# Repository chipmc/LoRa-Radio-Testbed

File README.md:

# LoRa-Radio-Testbed
# This repository includes the Arduino C programs for a simple LoRa testbed I created
# The Moteino LoRa Page has great information on this radio: https://lowpowerlab.com/moteino/#lora
#     - To use these sketches, you can download the libraries here:
#     - https://lowpowerlab.com/RadioHead_LowPowerLab.zip
# The hardware is described in the attached EAGLE files

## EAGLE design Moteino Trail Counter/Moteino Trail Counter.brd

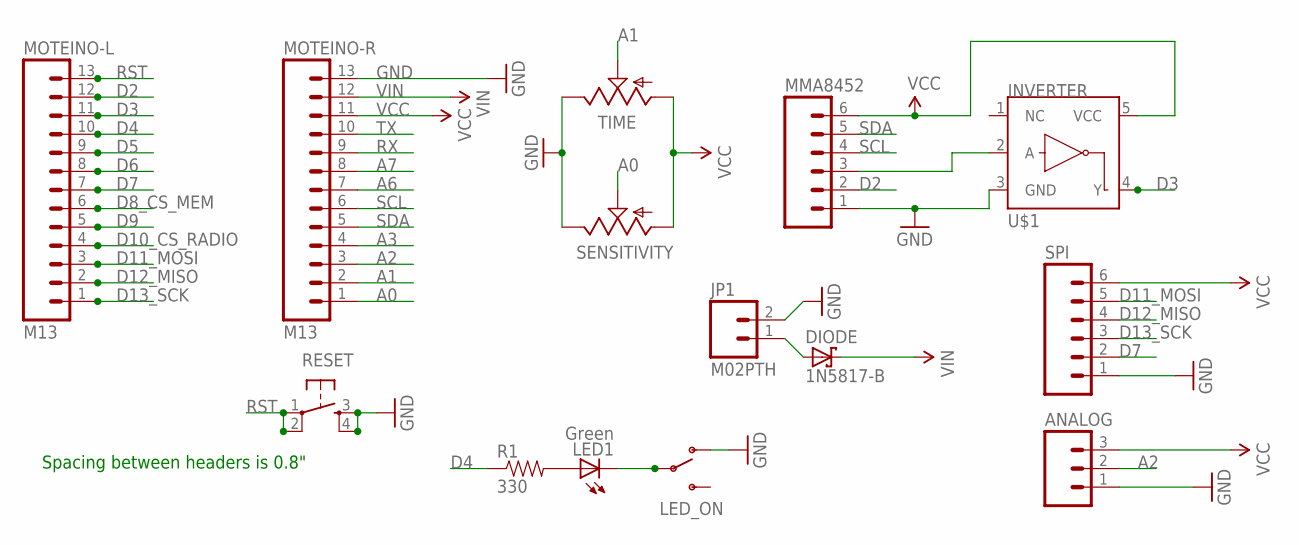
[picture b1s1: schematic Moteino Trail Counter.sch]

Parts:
ANALOG: M03LOCK; 1X03_LOCK
DIODE: 1N5817-B; DO41-7.6
JP1: M02PTH; 1X02
LED1: Green; LED3MM
LED_ON: SWITCH-SPDTPTH; SWITCH-SPDT
MMA8452: M06LOCK; 1X06_LOCK
MOTEINO-L: M13; 1X13
MOTEINO-R: M13; 1X13
R1: 330; AXIAL-0.3
RESET: TAC_SWITCHPTH; TACTILE-PTH
SENSITIVITY: TRIM_US-B25U; B25U
SPI: M06LOCK; 1X06_LOCK
TIME: TRIM_US-B25U; B25U
U$1: INVERTER; SOT23-5

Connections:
A0: MOTEINO-R.1, SENSITIVITY.S
A1: MOTEINO-R.2, TIME.S
A2: ANALOG.2, MOTEINO-R.3
A3: MOTEINO-R.4
A6: MOTEINO-R.7
A7: MOTEINO-R.8
D2: MMA8452.2, MOTEINO-L.12
D3: MOTEINO-L.11, U$1.4 (Y)
D4: MOTEINO-L.10, R1.P$1 (1)
D5: MOTEINO-L.9
D6: MOTEINO-L.8
D7: MOTEINO-L.7, SPI.2
D8_CS_MEM: MOTEINO-L.6
D9: MOTEINO-L.5
D10_CS_RADIO: MOTEINO-L.4
D11_MOSI: MOTEINO-L.3, SPI.5
D12_MISO: MOTEINO-L.2, SPI.4
D13_SCK: MOTEINO-L.1, SPI.3
GND: ANALOG.1, JP1.2, LED_ON.1 (O), MMA8452.1, MOTEINO-R.13, RESET.3, RESET.4, SENSITIVITY.E, SPI.1, TIME.E, U$1.3 (GND)
unnamed: DIODE.A, JP1.1
unnamed: LED1.A, R1.P$2 (2)
unnamed: MMA8452.3, U$1.2 (A)
unnamed: LED1.K (C), LED_ON.2
RST: MOTEINO-L.13, RESET.1, RESET.2
RX: MOTEINO-R.9
SCL: MMA8452.4, MOTEINO-R.6
SDA: MMA8452.5, MOTEINO-R.5
TX: MOTEINO-R.10
VCC: ANALOG.3, MMA8452.6, MOTEINO-R.11, SENSITIVITY.A, SPI.6, TIME.A, U$1.5 (VCC)
VIN: DIODE.C, MOTEINO-R.12

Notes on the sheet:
Spacing between headers is 0.8"

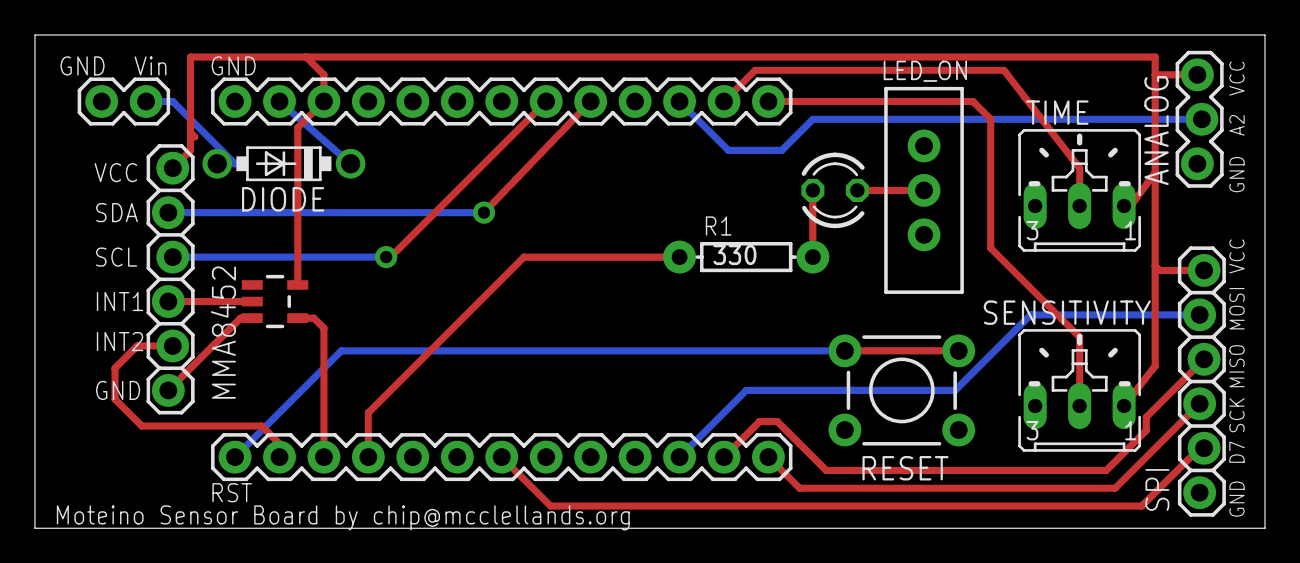
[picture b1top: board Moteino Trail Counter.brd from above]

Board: 2 copper layers, 70.3 x 28.2 mm, 14 parts (0 on the bottom side), 20 nets.

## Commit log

2016-09-13 Loaded Arduino and EAGLE files for Project
2016-09-13 Create README.md
    Added descriptions
2016-09-13 gitignore added

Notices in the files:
parts and their libraries:
SparkFun-Connectors: Licensing: Creative Commons ShareAlike 4.0 International - https://creativecommons.org/licenses/by-sa/4.0
